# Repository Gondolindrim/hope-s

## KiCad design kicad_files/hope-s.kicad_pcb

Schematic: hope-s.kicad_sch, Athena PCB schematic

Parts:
C1, C2, C3, C4, C10, C13: 100n; C_0402_1005Metric; Manufacturer Part Number CL05B104KB54PNC
C5: 10u; CP_EIA-3216-10_Kemet-I_Pad1.58x1.35mm_HandSolder; Manufacturer Part Number TAJA106K016RNJ
C6: 1u; C_0402_1005Metric; Manufacturer Part Number CL05A105KA5NQNC
C7: 10n; C_0402_1005Metric; Manufacturer Part Number CL05B103KB5NNNC
C8, C9: 15p; C_0402_1005Metric; Manufacturer Part Number 0402CG150J500NT
C11: 4.7u; C_0402_1005Metric; Manufacturer Part Number CL05A475MP5NRNC
C12: 10u; C_0402_1005Metric; Manufacturer Part Number CL05A106MQ5NUNC
C14: 1u; C_0805_2012Metric; Manufacturer Part Number 0805B105K500NT
D1, D3, D4, D5, D6, D7, D8, D9, D10, D11, D12, D13, D14, D15, D16, D17, D18, D19, D20, D21, D22, D23, D24, D25, D26, D27, D28, D29, D30, D31, D32, D33, D34, D35, D36, D37, D38, D39, D40, D41, D42, D43, D44, D45, D46, D47, D48, D49, D50, D51, D52, D53, D54, D55, D56, D57, D58, D59, D60, D61, D62, D63, D64, D65, D66, D67, D68, D69, D70, D71, D72, D73, D74, D75, D76, D77, D78, D79, D80, D81, D82, D83, D84, D85, D86, D87, D88, D89, D90, D91, D92, D93: 1N4148W; D_SOD-123; Manufacturer Part Number 1N4148W
D2: B5819W-SL; D_SOD-123; Manufacturer Part Number B5819W-SL
F1: nSMD100-16V; Fuse_1206_3216Metric; Manufacturer Part Number nSMD100-16V
GR1: Athena Label; athena_label_35x5.6
J1: EXTRA_PINS; PinHeader_1x6_P2.54mm_Vertical
J2: TYPE-C-31-M-12; Manufacturer Part Number TYPE-C-31-M-12
LED1, LED2, LED3: LED; LED_THT_2.54mm
Q1, Q2, Q3, Q4, Q6: 2N7002; SOT-23; Manufacturer Part Number 2N7002
Q5: AO3401A; SOT-23; Manufacturer Part Number Alpha & Omega Semicon
R1, R2: 4.7k; R_0402_1005Metric; Manufacturer Part Number 0402WGF4701TCE
R3: 1.5k; R_0402_1005Metric; Manufacturer Part Number 0402WGF1501TCE
R4: 51K; R_0402_1005Metric; Manufacturer Part Number 0402WGF1003TCE
R5: 330k; R_0402_1005Metric; Manufacturer Part Number 0402WGF3303TCE
R6: 1M; R_0402_1005Metric; Manufacturer Part Number 0402WGF1004TCE
R7, R11, R12, R21, R22, R25, R27: 10k; R_0402_1005Metric; Manufacturer Part Number 0402WGF1002TCE
R8, R9, R10: 100R; R_0402_1005Metric; Manufacturer Part Number 0402WGF1000TCE
R13, R14: 100k; R_0805_2012Metric; Manufacturer Part Number 0805W8F1003T5E
R15, R16: 5.1k; R_0402_1005Metric; Manufacturer Part Number 0402WGF5101TCE
R17: 0R; R_0805_2012Metric; Manufacturer Part Number RC0805JR-070RP
R18, R19: 1k; R_0402_1005Metric; Manufacturer Part Number 0402WGF1001TCE
R20, R23, R24, R26: 100; R_0402_1005Metric; Manufacturer Part Number 0402WGF1000TCE
SW1: K2-1187SQ-A4SW-06; Manufacturer Part Number K2-1187SQ-A4SW-06
SW2, SW3, SW4, SW5, SW6, SW7, SW8, SW9, SW10, SW11, SW12, SW13, SW14, SW15, SW16, SW17, SW18, SW19, SW20, SW21, SW22, SW23, SW24, SW25, SW26, SW27, SW28, SW29, SW30, SW32, SW33, SW34, SW35, SW37, SW38, SW39, SW40, SW41, SW42, SW43, SW44, SW45, SW46, SW47, SW48, SW51, SW52, SW53, SW54, SW55, SW56, SW57, SW58, SW59, SW60, SW61, SW62, SW64, SW65, SW66, SW70, SW71, SW72, SW73, SW74, SW75, SW76, SW77, SW78, SW79, SW80, SW82, SW83, SW92, SW95, SW96, SW97, SW102, SW104: MX Switch; MX100
SW31: MX Switch; MX200
SW36, SW49, SW98, SW99, SW101, SW103: MX Switch; MX150
SW50, SW84: MX Switch; MX175
SW63: MX Switch; MX225R
SW67, SW85, SW86, SW87, SW89, SW90, SW91, SW93, SW94: MX Switch; MX125
SW68: MX Switch; MX_ISOEnter
SW69: MX Switch; MX225
SW81: MX Switch; MX275
SW88: MX Switch; MX625R
SW100: MX Switch; MX700R
U1: BL24C256A-SFRC; TSSOP-8_4.4x3mm_P0.65mm; Manufacturer Part Number BL24C256A-SFRC
U2: STM32F411CEU6; STM_UFQFPN-48_LQFP-48-1EP_7x7mm_P0.5mm_HandSoldering_Therma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; Manufacturer Part Number STM32F411CEU6
U3: XC6206; SOT-23; Manufacturer Part Number XC6206P332MR
U4: USBLC6-2SC6; SOT-23-6; Manufacturer Part Number USBLC6-2SC6
X1: ARM JTAG; PinHeader_2x5_P2.54mm_Vertical_Staggered
Y1: 7325-0800A2010-00; Crystal_SMD_3225-4Pin_3.2x2.5mm; Manufacturer Part Number 7325-0800A2010-00

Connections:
3V3: C1.2, C2.1, C3.1, C4.2, C5.1, C6.1, C7.1, C10.2, D2.2 (A), J1.3, R1.1, R2.1, R3.1, R4.1, R14.2, SW1.1 (A), U1.8 (VCC), U2.1 (VBAT), U2.9 (VDDA/VREF+), U2.24 (VDD), U2.36 (VDD), U2.48 (VDD), U3.2 (VO), X1.7, X1.8
5V: C14.1, D2.1 (K), F1.2, J1.5, Q5.2 (S), R13.1, R22.2, U3.3 (VI)
BOOT0: C12.1, R5.1, R6.1, R7.2, U2.44 (BOOT0), X1.6
C0: SW2.2, SW18.2, SW36.2, SW50.1, SW67.2, SW69.2, SW85.1, SW86.2, SW98.2
C1: SW19.1, SW37.1, SW51.2, SW70.1, SW94.1, SW104.1
C2: SW3.1, SW20.1, SW38.1, SW52.1, SW71.2, SW87.1, SW99.1
C3: SW4.1, SW21.1, SW39.1, SW53.1, SW72.1
C4: SW5.1, SW22.1, SW40.1, SW54.1, SW73.1
C5: SW6.1, SW23.1, SW41.1, SW55.1, SW74.1
C6: SW7.1, SW24.1, SW42.1, SW56.1, SW75.1, SW88.1, SW100.2, U2.4 (PC15_OSC32OUT)
C7: SW8.1, SW25.1, SW43.1, SW57.1, SW76.1
C8: SW9.1, SW26.1, SW44.1, SW58.1, SW77.1
C9: SW10.1, SW27.1, SW45.1, SW59.1, SW78.1, SW89.2
C10: SW11.2, SW28.1, SW46.1, SW60.1, SW79.1, SW90.1, SW101.1
C11: SW12.2, SW29.1, SW47.1, SW61.1, SW80.1, SW91.1, SW102.1
C12: SW13.2, SW30.1, SW48.1, SW62.1, SW81.1, SW84.1
C13: SW14.1, SW31.1, SW35.1, SW49.1, SW63.1, SW68.1, SW82.2, SW93.1, SW103.1
C14: SW15.2, SW32.2, SW64.2, SW92.1, SW95.1
C15: SW16.1, SW33.1, SW65.1, SW83.1, SW96.1
C16: SW17.1, SW34.1, SW66.1, SW97.1
CAPS_INDICATOR: R20.1
D+: R3.2, U2.33 (PA12/USB_FS_DP), U4.3 (I/O2)
D-: U2.32 (PA11/USB_FS_DM), U4.1 (I/O1)
DBUS+: J2.A6 (D+), J2.B6 (D+), U4.4 (I/O2)
DBUS-: J2.A7 (D-), J2.B7 (D-), U4.6 (I/O1)
E-PA0: J1.1
E-PA1: J1.2
GND: C1.1, C2.2, C3.2, C4.1, C5.2, C6.2, C7.2, C8.2, C9.2, C10.1, C11.1, C12.2, C13.2, C14.2, J1.6, Q1.2 (S), Q2.2 (S), Q3.2 (S), Q4.2 (S), Q6.2 (S), R6.2, R11.1, R12.1, R13.2, R14.1, R17.2, R21.1, R25.1, R27.1, U1.1 (A0), U1.2 (A1), U1.3 (A2), U1.4 (GND), U1.7 (WP), U2.8 (VSSA), U2.23 (VSS), U2.35 (VSS), U2.47 (VSS), U3.1 (GND), X1.3, X1.4, X1.10, Y1.2, Y1.4
GND1: J2.A1 (GND), J2.B1 (GND), J2.S (SHIELD), R15.1, R16.2, R17.1, U4.2 (GND)
LED_PWM: R24.1, U2.19 (PB1)
LED_PWM_OUT: Q5.3 (D), R18.2, R19.2
NRST: C13.1, R9.2, U2.7 (NRST), X1.9
unnamed: D1.2 (A), R10.2, SW1.2 (B)
unnamed: D1.1 (K), R5.2
unnamed: D3.2 (A), SW2.1
unnamed: D4.2 (A), SW3.2
unnamed: D5.2 (A), SW4.2
unnamed: D6.2 (A), SW5.2
unnamed: D7.2 (A), SW6.2
unnamed: D8.2 (A), SW7.2
unnamed: D9.2 (A), SW8.2
unnamed: D10.2 (A), SW9.2
unnamed: D11.2 (A), SW10.2
unnamed: D12.2 (A), SW11.1
unnamed: D13.2 (A), SW12.1
unnamed: D14.2 (A), SW13.1
unnamed: D15.2 (A), SW14.2
unnamed: D16.2 (A), SW17.2
unnamed: D17.2 (A), SW16.2
unnamed: D18.2 (A), SW15.1
unnamed: D19.2 (A), SW18.1
unnamed: D20.2 (A), SW19.2
unnamed: D21.2 (A), SW20.2
unnamed: D22.2 (A), SW21.2
unnamed: D23.2 (A), SW22.2
unnamed: D24.2 (A), SW23.2
unnamed: D25.2 (A), SW24.2
unnamed: D26.2 (A), SW25.2
unnamed: D27.2 (A), SW26.2
unnamed: D28.2 (A), SW27.2
unnamed: D29.2 (A), SW28.2
unnamed: D30.2 (A), SW29.2
unnamed: D31.2 (A), SW30.2
unnamed: D32.2 (A), SW31.2, SW35.2
unnamed: D33.2 (A), SW34.2
unnamed: D34.2 (A), SW33.2
unnamed: D35.2 (A), SW32.1
unnamed: D36.2 (A), SW36.1
unnamed: D37.2 (A), SW37.2
unnamed: D38.2 (A), SW38.2
unnamed: D39.2 (A), SW39.2
unnamed: D40.2 (A), SW40.2
unnamed: D41.2 (A), SW41.2
unnamed: D42.2 (A), SW42.2
unnamed: D43.2 (A), SW43.2
unnamed: D44.2 (A), SW44.2
unnamed: D45.2 (A), SW45.2
unnamed: D46.2 (A), SW46.2
unnamed: D47.2 (A), SW47.2
unnamed: D48.2 (A), SW48.2
unnamed: D49.2 (A), SW49.2
unnamed: D50.2 (A), SW50.2, SW67.1
unnamed: D51.2 (A), SW51.1
unnamed: D52.2 (A), SW52.2
unnamed: D53.2 (A), SW53.2
unnamed: D54.2 (A), SW54.2
unnamed: D55.2 (A), SW55.2
unnamed: D56.2 (A), SW56.2
unnamed: D57.2 (A), SW57.2
unnamed: D58.2 (A), SW58.2
unnamed: D59.2 (A), SW59.2
unnamed: D60.2 (A), SW60.2
unnamed: D61.2 (A), SW61.2
unnamed: D62.2 (A), SW62.2
unnamed: D63.2 (A), SW63.2, SW68.2
unnamed: D64.2 (A), SW66.2
unnamed: D65.2 (A), SW65.2
unnamed: D66.2 (A), SW64.1
unnamed: D67.2 (A), SW69.1, SW85.2
unnamed: D68.2 (A), SW70.2
unnamed: D69.2 (A), SW71.1
unnamed: D70.2 (A), SW72.2
unnamed: D71.2 (A), SW73.2
unnamed: D72.2 (A), SW74.2
unnamed: D73.2 (A), SW75.2
unnamed: D74.2 (A), SW76.2
unnamed: D75.2 (A), SW77.2
unnamed: D76.2 (A), SW78.2
unnamed: D77.2 (A), SW79.2
unnamed: D78.2 (A), SW80.2
unnamed: D79.2 (A), SW81.2, SW84.2
unnamed: D80.2 (A), SW82.1
unnamed: D81.2 (A), SW83.2
unnamed: D82.2 (A), SW86.1, SW98.1
unnamed: D83.2 (A), SW87.2, SW99.2
unnamed: D84.2 (A), SW88.2, SW100.1
unnamed: D85.2 (A), SW89.1
unnamed: D86.2 (A), SW90.2, SW101.2
unnamed: D87.2 (A), SW91.2, SW102.2
unnamed: D88.2 (A), SW92.2
unnamed: D89.2 (A), SW93.2, SW103.2
unnamed: D90.2 (A), SW94.2, SW104.2
unnamed: D91.2 (A), SW97.2
unnamed: D92.2 (A), SW96.2
unnamed: D93.2 (A), SW95.2
unnamed: J2.A5 (CC1), R15.2
unnamed: J2.B5 (CC2), R16.1
unnamed: LED1.A, LED2.A, R18.1
unnamed: LED3.A, R19.1
unnamed: Q1.3 (D), R7.1
unnamed: Q1.1 (G), R8.2
unnamed: Q2.3 (D), R8.1, R9.1
unnamed: Q2.1 (G), R10.1, R11.2
unnamed: LED1.K, LED2.K, Q3.3 (D)
unnamed: Q3.1 (G), R20.2, R21.2
unnamed: LED3.K, Q4.3 (D)
unnamed: Q4.1 (G), R26.2, R27.2
unnamed: Q5.1 (G), R23.2
unnamed: Q6.3 (D), R22.1, R23.1
unnamed: Q6.1 (G), R24.2, R25.2
unnamed: R4.2, U2.31 (PA10)
unnamed: C11.2, U2.22 (VCAP_1)
PA9: J1.4, U2.30 (PA9/USB_FS_VBUS)
PB2/BOOT1: R12.2, U2.20 (PB2), X1.5
R0: D3.1 (K), D4.1 (K), D5.1 (K), D6.1 (K), D7.1 (K), D8.1 (K), D9.1 (K), D10.1 (K), D11.1 (K), D12.1 (K), D13.1 (K), D14.1 (K), D15.1 (K), D16.1 (K), D17.1 (K), D18.1 (K)
R1: D19.1 (K), D20.1 (K), D21.1 (K), D22.1 (K), D23.1 (K), D24.1 (K), D25.1 (K), D26.1 (K), D27.1 (K), D28.1 (K), D29.1 (K), D30.1 (K), D31.1 (K), D32.1 (K), D33.1 (K), D34.1 (K), D35.1 (K)
R2: D36.1 (K), D37.1 (K), D38.1 (K), D39.1 (K), D40.1 (K), D41.1 (K), D42.1 (K), D43.1 (K), D44.1 (K), D45.1 (K), D46.1 (K), D47.1 (K), D48.1 (K), D49.1 (K), D64.1 (K), D65.1 (K), D66.1 (K)
R3: D50.1 (K), D51.1 (K), D52.1 (K), D53.1 (K), D54.1 (K), D55.1 (K), D56.1 (K), D57.1 (K), D58.1 (K), D59.1 (K), D60.1 (K), D61.1 (K), D62.1 (K), D63.1 (K), D88.1 (K)
R4: D67.1 (K), D68.1 (K), D69.1 (K), D70.1 (K), D71.1 (K), D72.1 (K), D73.1 (K), D74.1 (K), D75.1 (K), D76.1 (K), D77.1 (K), D78.1 (K), D79.1 (K), D80.1 (K), D81.1 (K)
R5: D82.1 (K), D83.1 (K), D84.1 (K), D85.1 (K), D86.1 (K), D87.1 (K), D89.1 (K), D90.1 (K), D91.1 (K), D92.1 (K), D93.1 (K)
SCL: R2.2, U1.6 (SCL), U2.42 (PB6/I2C1_SCL)
SCROLL_INDICATOR: R26.1
SDA: R1.2, U1.5 (SDA), U2.43 (PB7/I2C1_SDA)
SWCLK: U2.37 (PA14/SWCLK), X1.2
SWDIO: U2.34 (PA12/SWDIO), X1.1
VBUS: F1.1, J2.A4 (VBUS), J2.B4 (VBUS), U4.5 (VBUS)
XTAL_IN: C9.1, U2.5 (PH0_OSCIN), Y1.3
XTAL_OUT: C8.1, U2.6 (PH1_OSCOUT), Y1.1

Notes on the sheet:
3V3
(**) PA9 jumper: a solderable jumper used to tie PA9 to VBUS. It is disconnected by default, hence PA9 is left floating
USB Connector
Spooky pin (*)
EEPROM
HARD RESET
(*) "Spooky pins": on STM32F4x1, pins A9 and B2 cannot be used for switch matrix: - A9 is meant to be used as a VBUS sensing. It has a undocumented internal pulldown resistor; - B2 is used as BOOT1 during bootup, so it needs an external pulldown for successful bootup; - B13 is locked by the SPI dri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
GRAPHICS
MCU
USB ESD
SWITCH MATRIX
LED BACKLIGHT

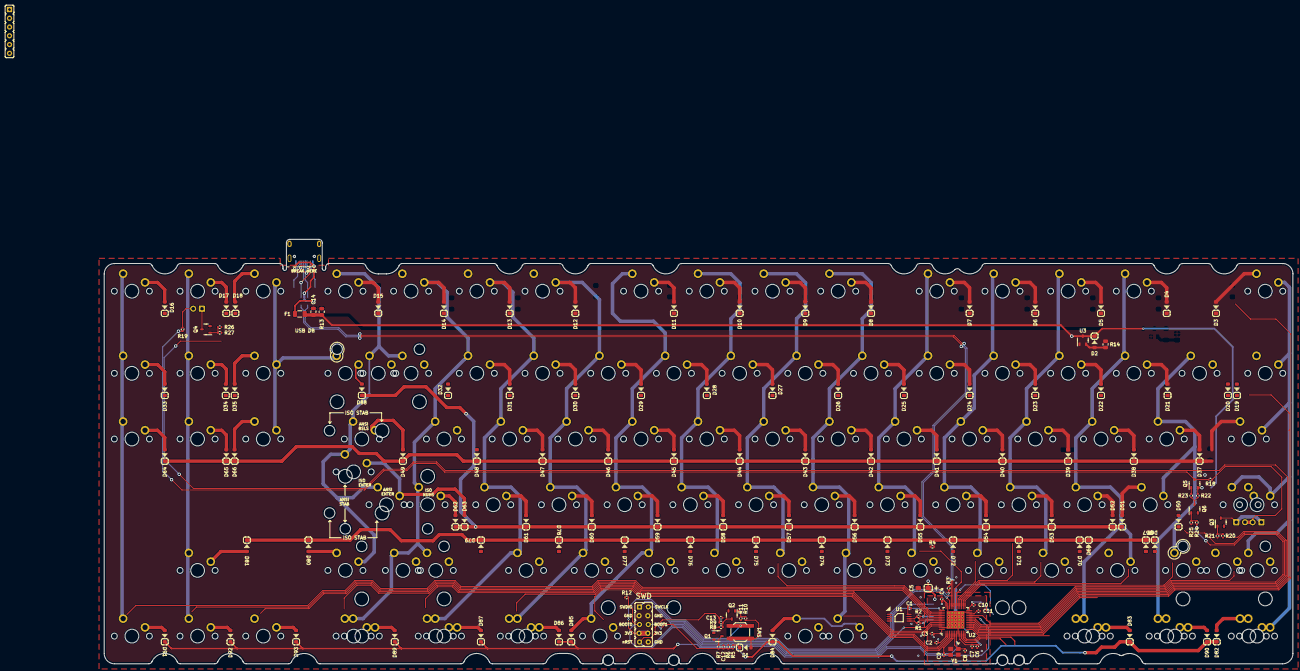
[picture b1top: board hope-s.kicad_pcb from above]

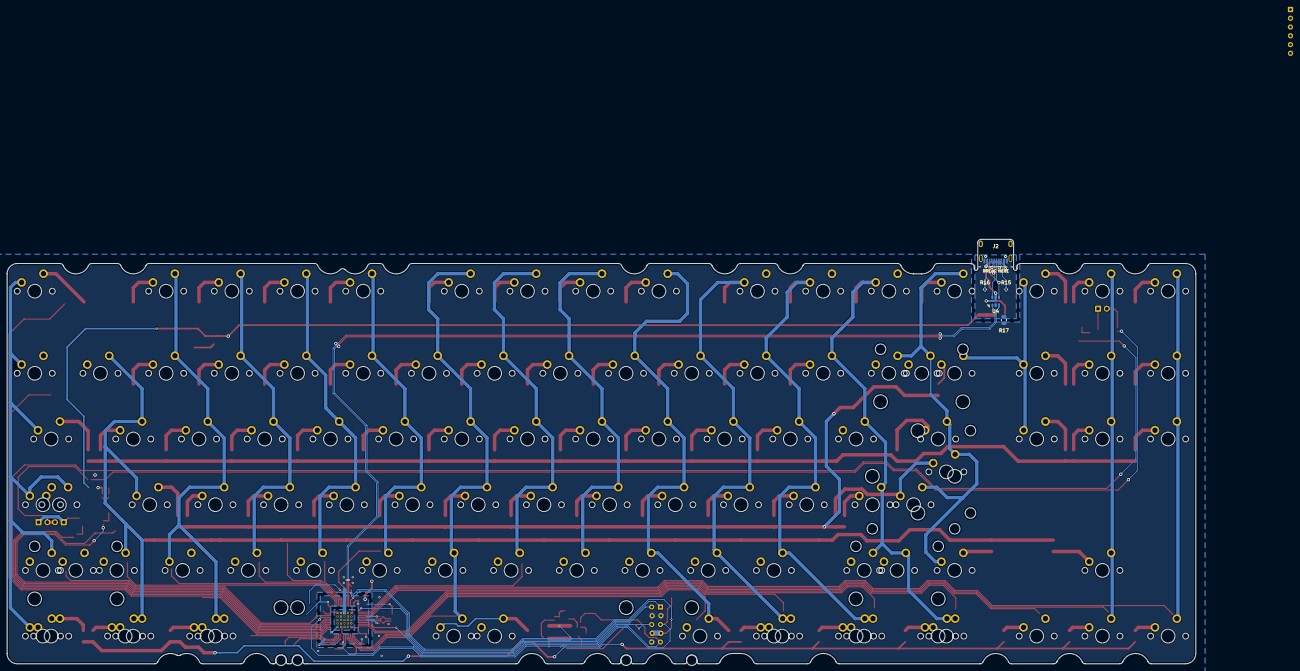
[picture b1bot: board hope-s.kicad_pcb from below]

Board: 2 copper layers, 344.7 x 123.1 mm, 255 parts (5 on the bottom side), 153 nets.

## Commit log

2025-09-26 Remove components lib
2025-09-26 DRC ran, checks ran
2025-09-26 Organize schematic and logos
2025-09-26 Release version, small corrections
